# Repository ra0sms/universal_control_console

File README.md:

## Universal Control Console (UCC)

The device can control any type of antenna switches. It has 8 independent programmable outputs and also can control [my version of receiving antenna K9AY](https://github.com/ra0sms/K9AY_with_wifi).

More information (in Russian, but Translate button still works) - https://ra0sms.com/ucc/

### [Schematic](KiCad/wired_console_k9ay/wired_console_k9ay.pdf)

### Outputs description

| DB25 pins | Description                                                  |
| --------- | ------------------------------------------------------------ |
| 1         | **K1** - open collector out for K9AY direction control       |
| 2         | **K2** - open collector out for K9AY direction control       |
| 3         | **K3** - open collector out for K9AY direction control       |
| 4         | **K4** - open collector out for K9AY direction control       |
| 5         | **300** - open collector out for K9AY load control           |
| 6         | **390** - open collector out for K9AY load control           |
| 7         | **430** - open collector out for K9AY load control           |
| 8         | **470** - open collector out for K9AY load control           |
| 9         | **510** - open collector out for K9AY load control           |
| 10        | **560** - open collector out for K9AY load control           |
| 11        | **PA_ON** - open collector out for K9AY preamplifier control |
| 12        | **12V** - output voltage (goes directly from power supply connector with the diode protection) |
| 13        | **GND** - Ground                                             |
| 14        | **OUT1** - First programmable output (when activated, has 12V out with fuse protection) |
| 15        | **OUT2** - Second programmable output (when activated, has 12V out with fuse protection) |
| 16        | **OUT3** - Third programmable output (when activated, has 12V out with fuse protection) |
| 17        | **OUT4** - Fourth programmable output (when activated, has 12V out with fuse protection) |
| 18        | **OUT5** - Fifth programmable output (when activated, has 12V out with fuse protection) |
| 19        | **OUT6** - Sixth programmable output (when activated, has 12V out with fuse protection) |
| 20        | **OUT7** - Seventh programmable output (when activated, has 12V out with fuse protection) |
| 21        | **OUT8** - Eighth programmable output (when activated, has 12V out with fuse protection) |
| 22        | **TX_GND** - when PTT activated, has connection to ground    |
| 23        | **$\overline{\text{PAON}}$** - when Preamp button pressed, has 12V out without any protection |
| 24        | **12V** - output voltage (goes directly from power supply connector with the diode protection) |
| 25        | **GND** - Ground                                             |

### Some photos

### GUI software for setting up outputs

You can choose outputs which will be activated when you push the buttons. Just connect USB to PC, choose com port and click Connect button.

[EXE-file (Windows OS)](gui/gui.zip)

[Python Script (Linux OS)](gui/gui.py)

### Antenna rotators emulator

UCC also can work with hamradio software, which use Yaesu rotator protocol. UCC can emulate a rotation at a given angle. You can use it with any supported software. For example [PST Rotator AZ](https://www.pstrotator.com/) and [DXLog](https://dxlog.net/).

### [Video with example or working](https://youtu.be/TXcX0s2ozSk)

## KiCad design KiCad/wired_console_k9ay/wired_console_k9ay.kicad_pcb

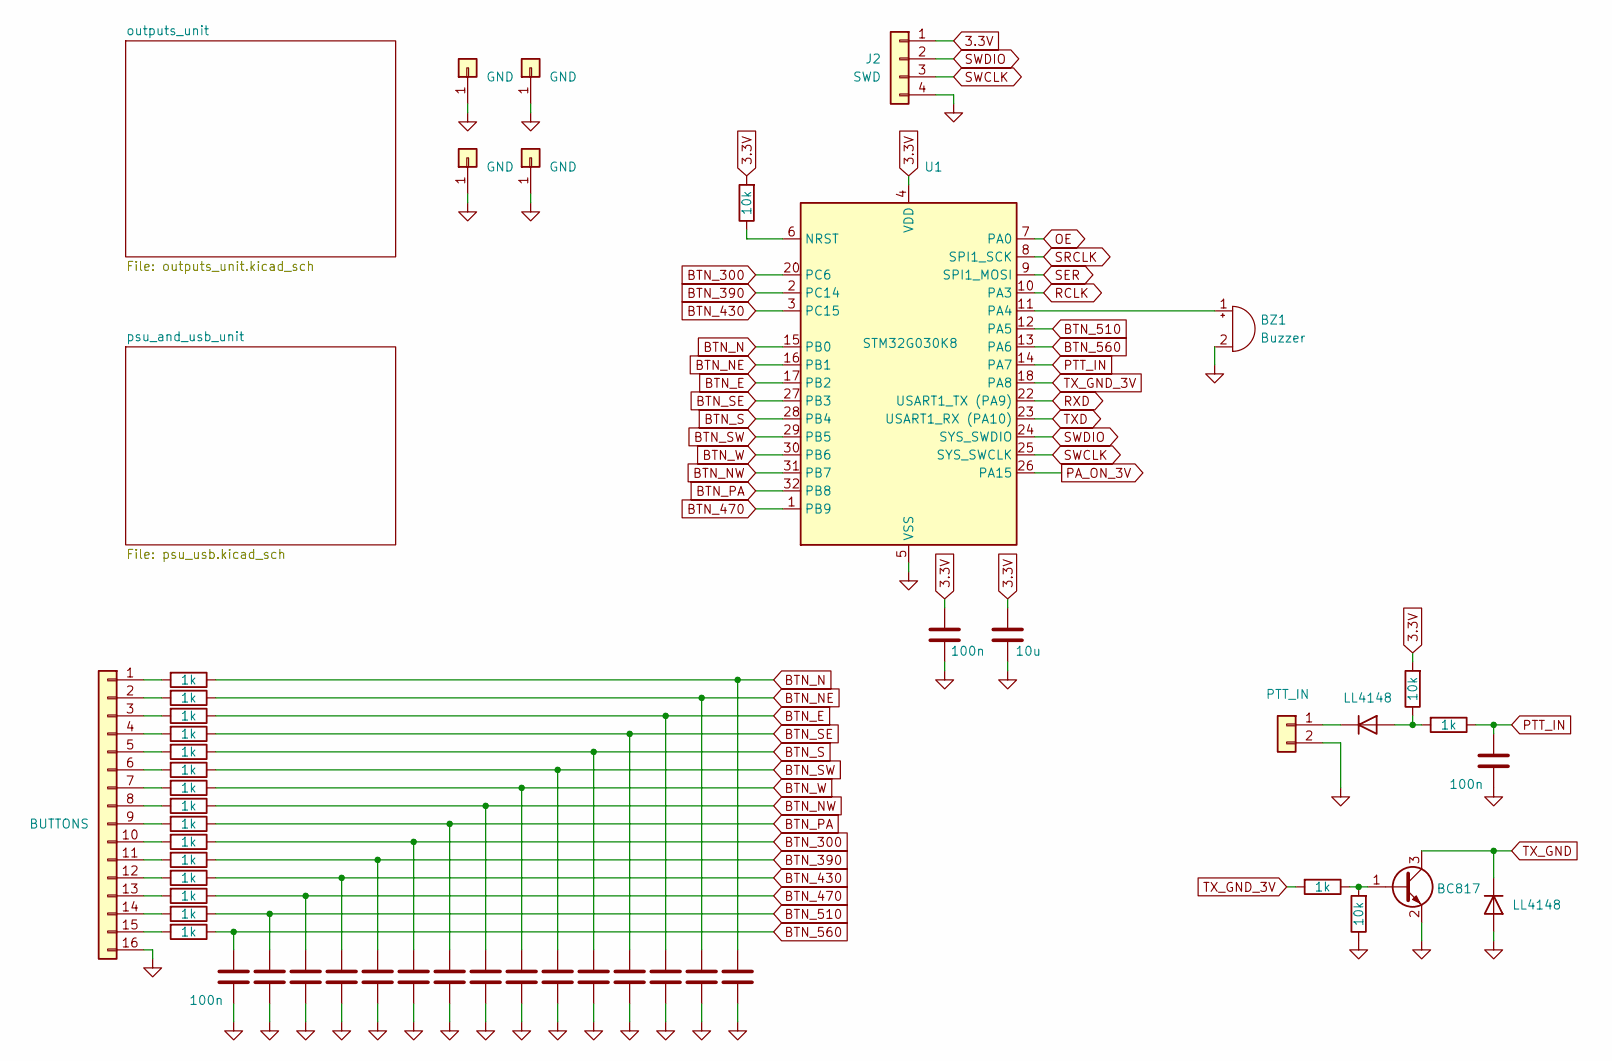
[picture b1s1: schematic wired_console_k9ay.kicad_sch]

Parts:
BZ1: Buzzer; Buzzer_12x9.5RM7.6
C1, C2, C3, C4, C5, C6, C7, C8, C9, C10, C11, C12, C13, C14, C15, C16, C37: 100n; C_1206_3216Metric_Pad1.33x1.80mm_HandSolder
C17: 10u; C_1206_3216Metric_Pad1.33x1.80mm_HandSolder
D3, D5: LL4148; D_MiniMELF
J1: BUTTONS; PinHeader_1x16_P2.54mm_Vertical
J2: SWD; PinSocket_1x04_P2.54mm_Vertical
J3: PTT_IN; PinHeader_1x02_P2.54mm_Vertical
J8, J9, J10, J11: GND; SolderWire-6sqmm_1x01_D3.5mm_OD7mm
Q2: BC817; SOT-23
R1, R2, R3, R4, R5, R6, R7, R8, R9, R10, R11, R12, R13, R14, R15, R34, R36: 1k; R_1206_3216Metric
R16, R33, R35: 10k; R_1206_3216Metric
U1: STM32G030K8; LQFP-32_7x7mm_P0.8mm

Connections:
3.3V: C16.1, C17.1, J2.1, R16.2, R33.2, U1.4 (VDD); also elsewhere on the board
BTN_300: C6.1, R10.1, U1.20 (PC6)
BTN_390: C5.1, R11.1, U1.2 (PC14)
BTN_430: C4.1, R12.1, U1.3 (PC15)
BTN_470: C3.1, R13.1, U1.1 (PB9)
BTN_510: C2.1, R14.1, U1.12 (PA5)
BTN_560: C1.1, R15.1, U1.13 (PA6)
BTN_E: C13.1, R3.1, U1.17 (PB2)
BTN_N: C15.1, R1.1, U1.15 (PB0)
BTN_NE: C14.1, R2.1, U1.16 (PB1)
BTN_NW: C8.1, R8.1, U1.31 (PB7)
BTN_PA: C7.1, R9.1, U1.32 (PB8)
BTN_S: C11.1, R5.1, U1.28 (PB4)
BTN_SE: C12.1, R4.1, U1.27 (PB3)
BTN_SW: C10.1, R6.1, U1.29 (PB5)
BTN_W: C9.1, R7.1, U1.30 (PB6)
GND: BZ1.2 (-), C1.2, C2.2, C3.2, C4.2, C5.2, C6.2, C7.2, C8.2, C9.2, C10.2, C11.2, C12.2, C13.2, C14.2, C15.2, C16.2, C17.2, C37.2, D5.2 (A), J1.16, J2.4, J3.2, J8.1, J9.1, J10.1, J11.1, Q2.2 (E), R35.1, U1.5 (VSS); also elsewhere on the board
unnamed: BZ1.1 (+), U1.11 (PA4)
unnamed: D3.2 (A), R33.1, R34.2
unnamed: D3.1 (K), J3.1
unnamed: J1.1, R1.2
unnamed: J1.2, R2.2
unnamed: J1.3, R3.2
unnamed: J1.4, R4.2
unnamed: J1.5, R5.2
unnamed: J1.6, R6.2
unnamed: J1.7, R7.2
unnamed: J1.8, R8.2
unnamed: J1.9, R9.2
unnamed: J1.10, R10.2
unnamed: J1.11, R11.2
unnamed: J1.12, R12.2
unnamed: J1.13, R13.2
unnamed: J1.14, R14.2
unnamed: J1.15, R15.2
unnamed: Q2.1 (B), R35.2, R36.1
unnamed: R16.1, U1.6 (NRST)
OE: U1.7 (PA0); also elsewhere on the board
PA_ON_3V: U1.26 (PA15); also elsewhere on the board
PTT_IN: C37.1, R34.1, U1.14 (PA7)
RCLK: U1.10 (PA3); also elsewhere on the board
RXD: U1.22 (USART1_TX (PA9)); also elsewhere on the board
SER: U1.9 (SPI1_MOSI); also elsewhere on the board
SRCLK: U1.8 (SPI1_SCK); also elsewhere on the board
SWCLK: J2.3, U1.25 (SYS_SWCLK)
SWDIO: J2.2, U1.24 (SYS_SWDIO)
TXD: U1.23 (USART1_RX (PA10)); also elsewhere on the board
TX_GND: D5.1 (K), Q2.3 (C); also elsewhere on the board
TX_GND_3V: R36.2, U1.18 (PA8)

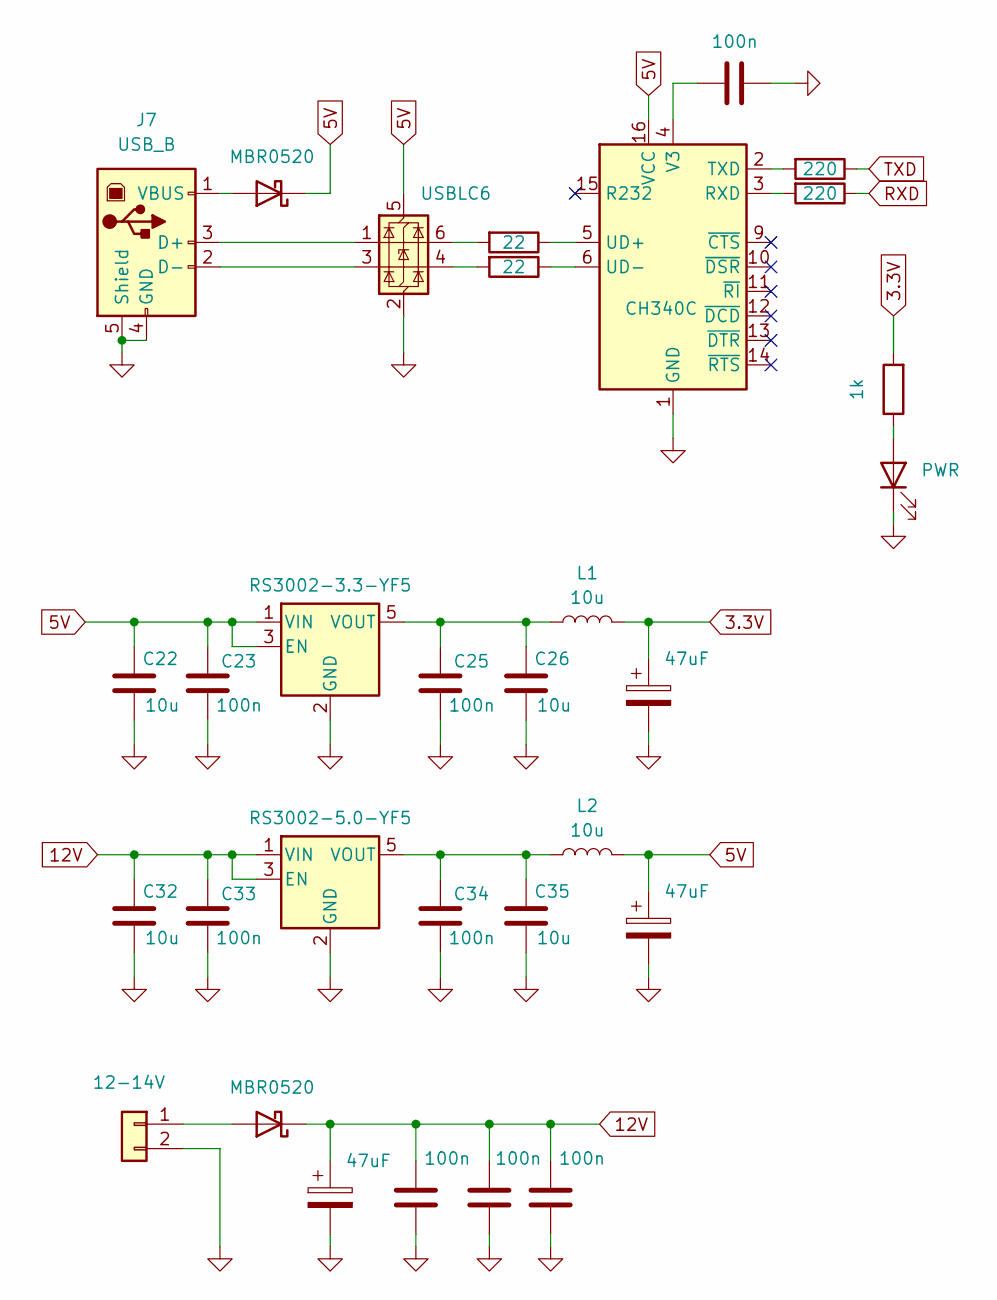
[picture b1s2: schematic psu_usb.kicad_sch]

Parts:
C18, C27, C36: 47uF; CP_Radial_D5.0mm_P2.50mm
C19, C20, C21, C24: 100n; C_1206_3216Metric
C22, C26, C32, C35: 10u; C_1206_3216Metric_Pad1.33x1.80mm_HandSolder
C23, C25, C33, C34: 100n; C_1206_3216Metric_Pad1.33x1.80mm_HandSolder
D1, D2: MBR0520; D_SOD-123
D4: PWR; LED_1206_3216Metric
J4: 12-14V; PinHeader_1x02_P2.54mm_Vertical
J7: USB_B; USB_B_Lumberg_2411_02_Horizontal
L1, L2: 10u; L_1206_3216Metric
R17, R18: 22; R_1206_3216Metric
R19, R20: 220; R_1206_3216Metric
R21: 1k; R_1206_3216Metric
U2: USBLC6; SOT-23-6
U3: CH340C; SOIC-16_3.9x9.9mm_P1.27mm
U4: RS3002-3.3-YF5; SOT-23-5
U12: RS3002-5.0-YF5; SOT-23-5

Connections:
3.3V: C27.1, L1.2, R21.2; also elsewhere on the board
5V: C22.1, C23.1, C36.1, D2.1 (K), L2.2, U2.5 (VBUS), U3.16 (VCC), U4.1 (VIN), U4.3 (EN); also elsewhere on the board
12V: C18.1, C19.1, C20.1, C21.1, C32.1, C33.1, D1.1 (K), U12.1 (VIN), U12.3 (EN); also elsewhere on the board
GND: C18.2, C19.2, C20.2, C21.2, C22.2, C23.2, C24.2, C25.2, C26.2, C27.2, C32.2, C33.2, C34.2, C35.2, C36.2, D4.1 (K), J4.2, J7.4 (GND), J7.5 (Shield), U2.2 (GND), U3.1 (GND), U4.2 (GND), U12.2 (GND); also elsewhere on the board
unnamed: D1.2 (A), J4.1
unnamed: D2.2 (A), J7.1 (VBUS)
unnamed: D4.2 (A), R21.1
unnamed: J7.3 (D+), U2.1 (I/O1)
unnamed: J7.2 (D-), U2.3 (I/O2)
unnamed: R17.2, U2.6 (I/O1)
unnamed: R18.2, U2.4 (I/O2)
unnamed: R20.2, U3.3 (RXD)
unnamed: R19.2, U3.2 (TXD)
unnamed: R17.1, U3.5 (UD+)
unnamed: R18.1, U3.6 (UD-)
unnamed: C24.1, U3.4 (V3)
unnamed: C25.1, C26.1, L1.1, U4.5 (VOUT)
unnamed: C34.1, C35.1, L2.1, U12.5 (VOUT)
RXD: R20.1; also elsewhere on the board
TXD: R19.1; also elsewhere on the board

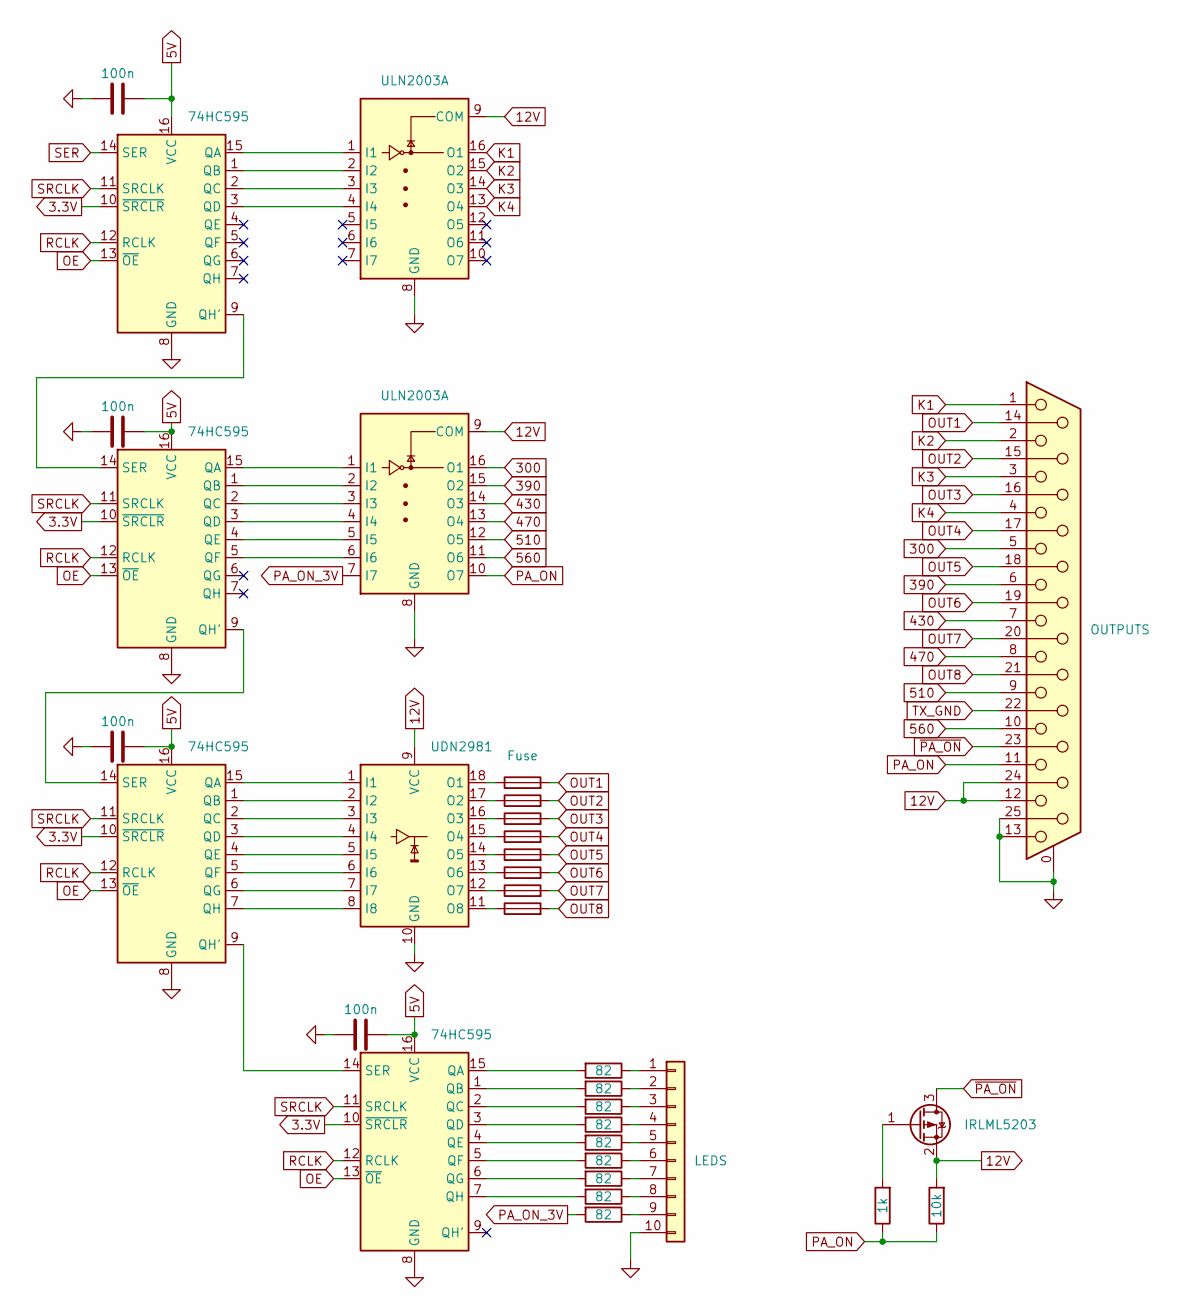
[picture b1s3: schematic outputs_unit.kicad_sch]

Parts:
C28, C29, C30, C31: 100n; C_1206_3216Metric
F1, F2, F3, F4, F5, F6, F7, F8: Fuse; R_1206_3216Metric
J5: LEDS; PinSocket_1x10_P2.54mm_Vertical
J6: OUTPUTS; DSUB-25_Socket_Horizontal_P2.77x2.84mm_EdgePinOffset4.94mm_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
Q1: IRLML5203; SOT-23
R22, R23, R24, R25, R26, R27, R28, R29, R30: 82; R_1206_3216Metric
R31: 1k; R_1206_3216Metric
R32: 10k; R_1206_3216Metric
U5, U6, U7, U11: 74HC595; SOIC-16_3.9x9.9mm_P1.27mm
U8, U9: ULN2003A; SOIC-16_3.9x9.9mm_P1.27mm
U10: UDN2981; DIP-18_W7.62mm_LongPads

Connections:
3.3V: U5.10 (~SRCLR), U6.10 (~SRCLR), U7.10 (~SRCLR), U11.10 (~SRCLR); also elsewhere on the board
5V: C28.2, C29.2, C30.2, C31.2, U5.16 (VCC), U6.16 (VCC), U7.16 (VCC), U11.16 (VCC); also elsewhere on the board
12V: J6.12, J6.24, Q1.2 (S), R32.2, U8.9 (COM), U9.9 (COM), U10.9 (VCC); also elsewhere on the board
300: J6.5, U9.16 (O1)
390: J6.6, U9.15 (O2)
430: J6.7, U9.14 (O3)
470: J6.8, U9.13 (O4)
510: J6.9, U9.12 (O5)
560: J6.10, U9.11 (O6)
GND: C28.1, C29.1, C30.1, C31.1, J5.10, J6.0 (PAD), J6.13, J6.25, U5.8 (GND), U6.8 (GND), U7.8 (GND), U8.8 (GND), U9.8 (GND), U10.10 (GND), U11.8 (GND); also elsewhere on the board
K1: J6.1, U8.16 (O1)
K2: J6.2, U8.15 (O2)
K3: J6.3, U8.14 (O3)
K4: J6.4, U8.13 (O4)
unnamed: J5.1, R22.1
unnamed: J5.2, R23.1
unnamed: J5.3, R24.1
unnamed: J5.4, R25.1
unnamed: J5.5, R26.1
unnamed: J5.6, R27.1
unnamed: J5.7, R28.1
unnamed: J5.8, R29.1
unnamed: J5.9, R30.1
unnamed: Q1.1 (G), R31.2
unnamed: U5.15 (QA), U8.1 (I1)
unnamed: U5.1 (QB), U8.2 (I2)
unnamed: U5.2 (QC), U8.3 (I3)
unnamed: U5.3 (QD), U8.4 (I4)
unnamed: U5.9 (QH'), U6.14 (SER)
unnamed: U6.15 (QA), U9.1 (I1)
unnamed: U6.1 (QB), U9.2 (I2)
unnamed: U6.2 (QC), U9.3 (I3)
unnamed: U6.3 (QD), U9.4 (I4)
unnamed: U6.4 (QE), U9.5 (I5)
unnamed: U6.5 (QF), U9.6 (I6)
unnamed: U6.9 (QH'), U7.14 (SER)
unnamed: U7.15 (QA), U10.1 (I1)
unnamed: U7.1 (QB), U10.2 (I2)
unnamed: U7.2 (QC), U10.3 (I3)
unnamed: U7.3 (QD), U10.4 (I4)
unnamed: U7.4 (QE), U10.5 (I5)
unnamed: U7.5 (QF), U10.6 (I6)
unnamed: U7.6 (QG), U10.7 (I7)
unnamed: U7.7 (QH), U10.8 (I8)
unnamed: F1.1, U10.18 (O1)
unnamed: F2.1, U10.17 (O2)
unnamed: F3.1, U10.16 (O3)
unnamed: F4.1, U10.15 (O4)
unnamed: F5.1, U10.14 (O5)
unnamed: F6.1, U10.13 (O6)
unnamed: F7.1, U10.12 (O7)
unnamed: F8.1, U10.11 (O8)
unnamed: R22.2, U11.15 (QA)
unnamed: R23.2, U11.1 (QB)
unnamed: R24.2, U11.2 (QC)
unnamed: R25.2, U11.3 (QD)
unnamed: R26.2, U11.4 (QE)
unnamed: R27.2, U11.5 (QF)
unnamed: R28.2, U11.6 (QG)
unnamed: R29.2, U11.7 (QH)
unnamed: U7.9 (QH'), U11.14 (SER)
OE: U5.13 (~OE), U6.13 (~OE), U7.13 (~OE), U11.13 (~OE); also elsewhere on the board
OUT1: F1.2, J6.14
OUT2: F2.2, J6.15
OUT3: F3.2, J6.16
OUT4: F4.2, J6.17
OUT5: F5.2, J6.18
OUT6: F6.2, J6.19
OUT7: F7.2, J6.20
OUT8: F8.2, J6.21
PA_ON: J6.11, R31.1, R32.1, U9.10 (O7)
PA_ON_3V: R30.2, U9.7 (I7); also elsewhere on the board
RCLK: U5.12 (RCLK), U6.12 (RCLK), U7.12 (RCLK), U11.12 (RCLK); also elsewhere on the board
SER: U5.14 (SER); also elsewhere on the board
SRCLK: U5.11 (SRCLK), U6.11 (SRCLK), U7.11 (SRCLK), U11.11 (SRCLK); also elsewhere on the board
TX_GND: J6.22; also elsewhere on the board
~PA_ON: J6.23, Q1.3 (D)

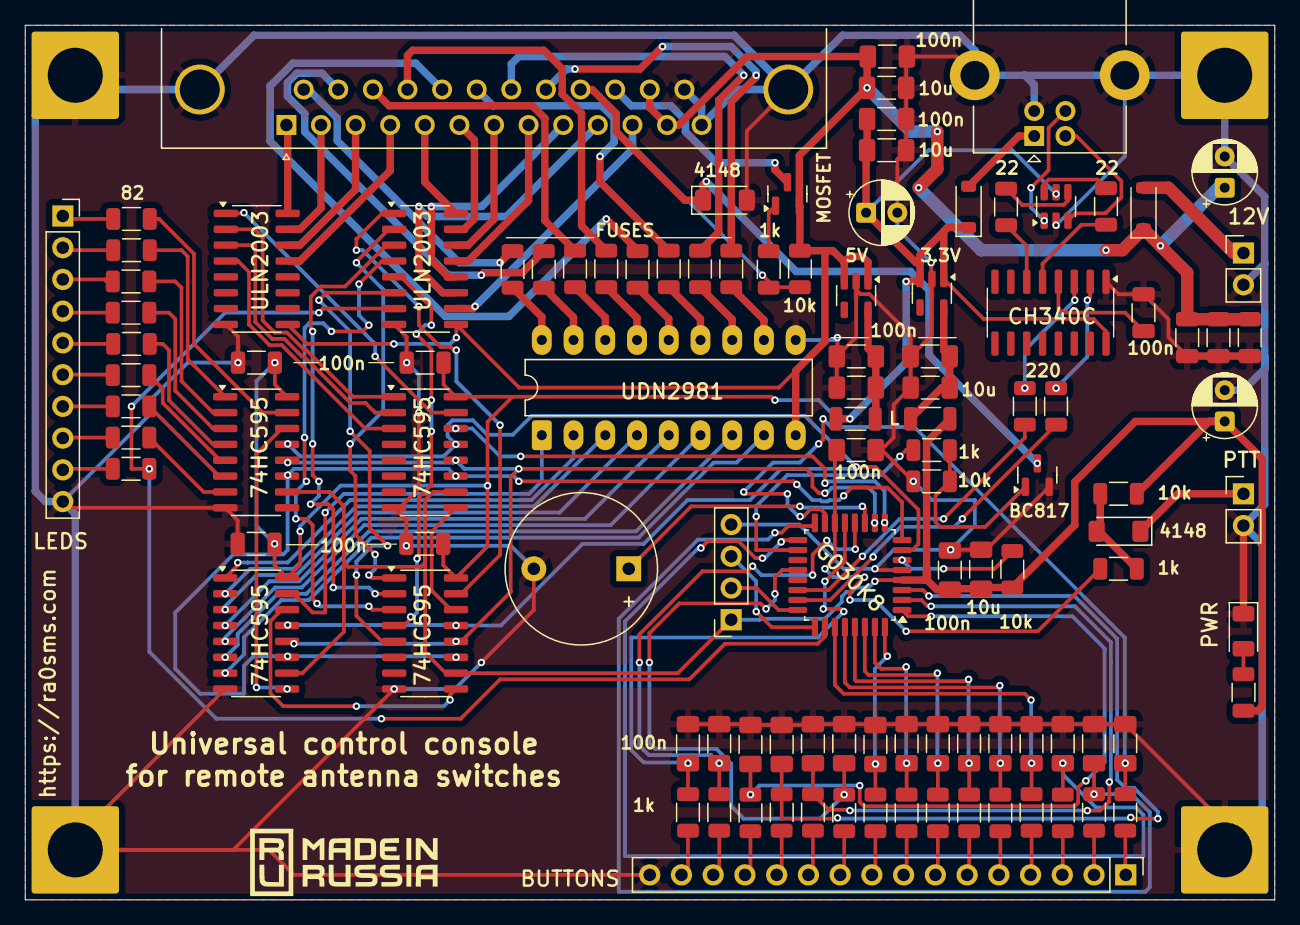
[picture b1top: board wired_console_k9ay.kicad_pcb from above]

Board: 2 copper layers, 100.0 x 70.0 mm, 114 parts (0 on the bottom side), 132 nets.

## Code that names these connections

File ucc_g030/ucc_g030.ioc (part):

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Mcu.Name=STM32G030K(6-8)Tx
Mcu.Package=LQFP32
Mcu.UserName=STM32G030K8Tx
PA0.GPIOParameters=GPIO_Label
PA0.GPIO_Label=OE
PA0.Signal=GPIO_Output
PA1.Mode=TX_Only_Simplex_Unidirect_Master
PA1.Signal=SPI1_SCK
PA10\ [PA12].Mode=Asynchronous
PA10\ [PA12].Signal=USART1_RX
PA13.Mode=Serial_Wire
PA13.Signal=SYS_SWDIO
PA14-BOOT0.Mode=Serial_Wire
PA14-BOOT0.Signal=SYS_SWCLK
PA15.GPIOParameters=GPIO_Label
PA15.GPIO_Label=PA_ON
PA15.Signal=GPIO_Output
PA2.Mode=TX_Only_Simplex_Unidirect_Master
PA2.Signal=SPI1_MOSI
PA3.GPIOParameters=GPIO_Label
PA3.GPIO_Label=RCLK
PA3.Signal=GPIO_Output
PA4.GPIOParameters=GPIO_Label
PA4.GPIO_Label=BUZZER
PA4.Signal=GPIO_Output
PA5.GPIOParameters=GPIO_PuPd,GPIO_Label
PA5.GPIO_Label=BTN_510
PA5.GPIO_PuPd=GPIO_PULLUP
PA5.Signal=GPIO_Input
PA6.GPIOParameters=GPIO_PuPd,GPIO_Label
PA6.GPIO_Label=BTN_560
PA6.GPIO_PuPd=GPIO_PULLUP
PA6.Signal=GPIO_Input
PA7.GPIOParameters=GPIO_PuPd,GPIO_Label
PA7.GPIO_Label=PTT_IN
PA7.GPIO_PuPd=GPIO_PULLUP
PA7.Signal=GPIO_Input
PA8.GPIOParameters=GPIO_Label
PA8.GPIO_Label=TX_GND
PA8.Signal=GPIO_Output
PA9\ [PA11].Mode=Asynchronous
PA9\ [PA11].Signal=USART1_TX
PB0.GPIOParameters=GPIO_PuPd,GPIO_Label
PB0.GPIO_Label=BTN_N
PB0.GPIO_PuPd=GPIO_PULLUP
PB0.Signal=GPIO_Input
PB1.GPIOParameters=GPIO_PuPd,GPIO_Label
PB1.GPIO_Label=BTN_NE
PB1.GPIO_PuPd=GPIO_PULLUP
PB1.Signal=GPIO_Input
PB2.GPIOParameters=GPIO_PuPd,GPIO_Label
PB2.GPIO_Label=BTN_E
PB2.GPIO_PuPd=GPIO_PULLUP
PB2.Signal=GPIO_Input
PB3.GPIOParameters=GPIO_PuPd,GPIO_Label
PB3.GPIO_Label=BTN_SE
PB3.GPIO_PuPd=GPIO_PULLUP
PB3.Signal=GPIO_Input
PB4.GPIOParameters=GPIO_PuPd,GPIO_Label
PB4.GPIO_Label=BTN_S
PB4.GPIO_PuPd=GPIO_PULLUP
PB4.Signal=GPIO_Input
PB5.GPIOParameters=GPIO_PuPd,GPIO_Label
PB5.GPIO_Label=BTN_SW
PB5.GPIO_PuPd=GPIO_PULLUP
PB5.Signal=GPIO_Input
PB6.GPIOParameters=GPIO_PuPd,GPIO_Label
PB6.GPIO_Label=BTN_W
PB6.GPIO_PuPd=GPIO_PULLUP
PB6.Signal=GPIO_Input
PB7.GPIOParameters=GPIO_PuPd,GPIO_Label
PB7.GPIO_Label=BTN_NW
PB7.GPIO_PuPd=GPIO_PULLUP
PB7.Signal=GPIO_Input
PB8.GPIOParameters=GPIO_PuPd,GPIO_Label
PB8.GPIO_Label=BTN_PA
PB8.GPIO_PuPd=GPIO_PULLUP
PB8.Signal=GPIO_Input
PB9.GPIOParameters=GPIO_PuPd,GPIO_Label
PB9.GPIO_Label=BTN_470
PB9.GPIO_PuPd=GPIO_PULLUP
PB9.Signal=GPIO_Input
PC14-OSC32_IN\ (PC14).GPIOParameters=GPIO_PuPd,GPIO_Label
PC14-OSC32_IN\ (PC14).GPIO_Label=BTN_390
PC14-OSC32_IN\ (PC14).GPIO_PuPd=GPIO_PULLUP
PC14-OSC32_IN\ (PC14).Signal=GPIO_Input
PC15-OSC32_OUT\ (PC15).GPIOParameters=GPIO_PuPd,GPIO_Label
PC15-OSC32_OUT\ (PC15).GPIO_Label=BTN_430
PC15-OSC32_OUT\ (PC15).GPIO_PuPd=GPIO_PULLUP
PC15-OSC32_OUT\ (PC15).Signal=GPIO_Input
PC6.GPIOParameters=GPIO_PuPd,GPIO_Label
PC6.GPIO_Label=BTN_300
PC6.GPIO_PuPd=GPIO_PULLUP
PC6.Signal=GPIO_Input
RCC.HSE_VALUE=8000000
RCC.SYSCLKFreq_VALUE=64000000
RCC.SYSCLKSource=RCC_SYSCLKSOURCE_PLLCLK
board=custom

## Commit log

2025-07-08 add gui
2025-07-09 fix some issues
2025-07-09 add license
2025-07-09 add pics
2025-07-10 add video
2025-07-10 add readme
2025-07-10 add link to youtube
2025-07-10 add link on gui at readme
2025-07-10 add gui.zip
